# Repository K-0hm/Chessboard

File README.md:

# TactBoard
Code for a chessboard with light and capacitance Touch Sensors.

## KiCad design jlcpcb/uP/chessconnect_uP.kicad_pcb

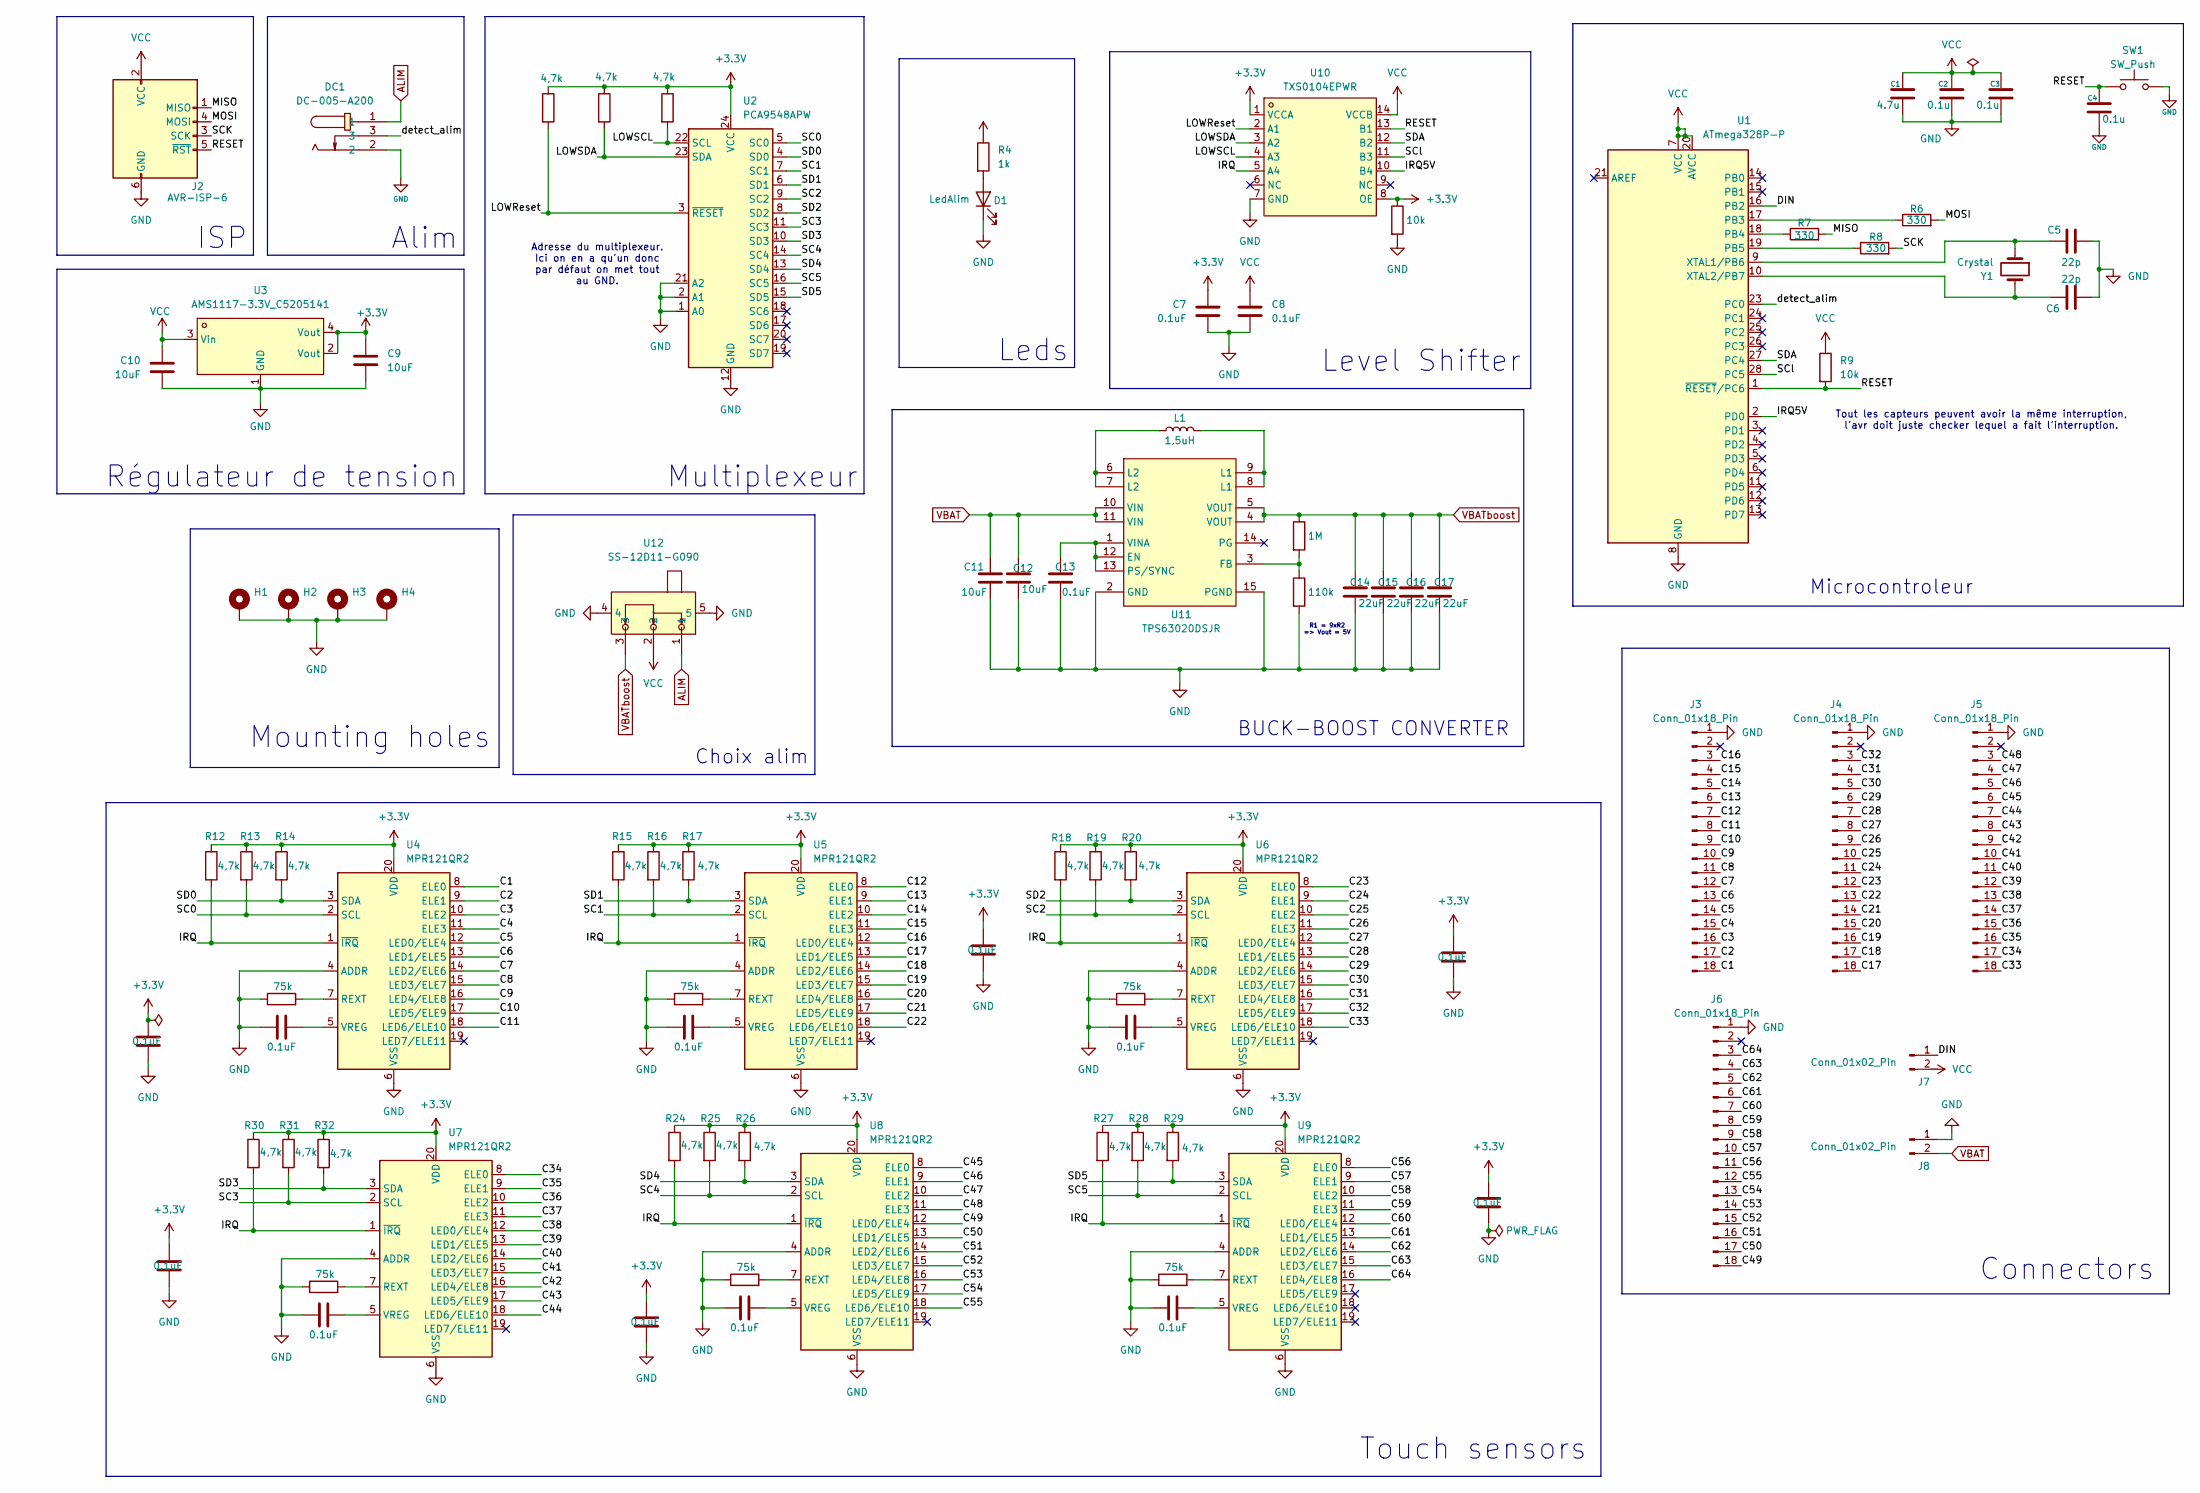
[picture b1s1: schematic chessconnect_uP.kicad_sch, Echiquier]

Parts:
C1: 4.7u; C_0603_1608Metric_Pad1.08x0.95mm_HandSolder
C2, C3, C4: 0.1u; C_0603_1608Metric_Pad1.08x0.95mm_HandSolder
C5, C6: 22p; C_0603_1608Metric_Pad1.08x0.95mm_HandSolder
C7, C8, C13, C18, C19, C20, C21, C22, C23, C24, C25, C26, C27, C28, C29: 0.1uF; C_0603_1608Metric_Pad1.08x0.95mm_HandSolder
C9, C10, C11, C12: 10uF; C_0603_1608Metric_Pad1.08x0.95mm_HandSolder
C14, C15, C16, C17: 22uF; C_0603_1608Metric_Pad1.08x0.95mm_HandSolder
D1: LedAlim; LED_0201_0603Metric_Pad0.64x0.40mm_HandSolder
DC1: DC-005-A200; DC-IN-TH_DC-005-A200; MPN DC-005-A200; LCSC Part C720557
H1, H2, H3, H4: MountingHole_Pad; MountingHole_3.2mm_M3_DIN965_Pad
J2: AVR-ISP-6; PinSocket_2x03_P2.54mm_Vertical
J3, J4, J5, J6: Conn_01x18_Pin; FPC-SMD_18P-P1.00_XUNPU_FPC-1.0FX-18PWCR-H20
J7, J8: Conn_01x02_Pin; PinHeader_1x02_P2.54mm_Horizontal
L1: 1,5uH; IND-SMD_L4.0-W4.0-A
R1, R2, R3, R12, R13, R14, R15, R16, R17, R18, R19, R20, R24, R25, R26, R27, R28, R29, R30, R31, R32: 4,7k; R_0603_1608Metric_Pad0.98x0.95mm_HandSolder
R4: 1k; R_0603_1608Metric_Pad0.98x0.95mm_HandSolder
R5, R9: 10k; R_0603_1608Metric_Pad0.98x0.95mm_HandSolder
R6, R7, R8: 330; R_0603_1608Metric_Pad0.98x0.95mm_HandSolder
R10: 1M; R_0603_1608Metric_Pad0.98x0.95mm_HandSolder
R11: 110k; R_0603_1608Metric_Pad0.98x0.95mm_HandSolder
R21, R22, R23, R33, R34, R35: 75k; R_0603_1608Metric_Pad0.98x0.95mm_HandSolder
SW1: SW_Push; SW_PUSH_6mm_H8mm
U1: ATmega328P-P; DIP-28_W7.62mm
U2: PCA9548APW; TSSOP-24_L7.8-W4.4-P0.65-LS6.4-BL
U3: AMS1117-3.3V_C5205141; SOT-223-3_L6.5-W3.4-P2.30-LS7.0-BR; MPN AMS1117-3.3V; LCSC Part C5205141
U4, U5, U6, U7, U8, U9: MPR121QR2; UQFN-20_3x3mm_P0.4mm
U10: TXS0104EPWR; TSSOP-14_L5.0-W4.4-P0.65-LS6.4-BL; MPN TXS0104EPWR; LCSC Part C44955
U11: TPS63020DSJR; VSON-14_L4.0-W3.0-P0.50-BL-EP_TI_DSJ; MPN TPS63020DSJR; LCSC Part C15483
U12: SS-12D11-G090; SW-TH_5P-P4.70_SS-12D11-G090; MPN SS-12D11-G090; LCSC Part C17179532
Y1: Crystal; Crystal_HC49-4H_Vertical

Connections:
+3.3V: C7.1, C9.1, C18.2, C19.2, C23.2, C24.2, C25.2, C29.2, R1.1, R2.1, R3.1, R5.1, R12.1, R13.1, R14.1, R15.1, R16.1, R17.1, R18.1, R19.1, R20.1, R24.1, R25.1, R26.1, R27.1, R28.1, R29.1, R30.1, R31.1, R32.1, U2.24 (VCC), U3.2 (Vout), U3.4 (Vout), U4.20 (VDD), U5.20 (VDD), U6.20 (VDD), U7.20 (VDD), U8.20 (VDD), U9.20 (VDD), U10.1 (VCCA), U10.8 (OE)
/C1: J3.18, U4.8 (ELE0)
/C2: J3.17, U4.9 (ELE1)
/C3: J3.16, U4.10 (ELE2)
/C4: J3.15, U4.11 (ELE3)
/C5: J3.14, U4.12 (LED0/ELE4)
/C6: J3.13, U4.13 (LED1/ELE5)
/C7: J3.12, U4.14 (LED2/ELE6)
/C8: J3.11, U4.15 (LED3/ELE7)
/C9: J3.10, U4.16 (LED4/ELE8)
/C10: J3.9, U4.17 (LED5/ELE9)
/C11: J3.8, U4.18 (LED6/ELE10)
/C12: J3.7, U5.8 (ELE0)
/C13: J3.6, U5.9 (ELE1)
/C14: J3.5, U5.10 (ELE2)
/C15: J3.4, U5.11 (ELE3)
/C16: J3.3, U5.12 (LED0/ELE4)
/C17: J4.18, U5.13 (LED1/ELE5)
/C18: J4.17, U5.14 (LED2/ELE6)
/C19: J4.16, U5.15 (LED3/ELE7)
/C20: J4.15, U5.16 (LED4/ELE8)
/C21: J4.14, U5.17 (LED5/ELE9)
/C22: J4.13, U5.18 (LED6/ELE10)
/C23: J4.12, U6.8 (ELE0)
/C24: J4.11, U6.9 (ELE1)
/C25: J4.10, U6.10 (ELE2)
/C26: J4.9, U6.11 (ELE3)
/C27: J4.8, U6.12 (LED0/ELE4)
/C28: J4.7, U6.13 (LED1/ELE5)
/C29: J4.6, U6.14 (LED2/ELE6)
/C30: J4.5, U6.15 (LED3/ELE7)
/C31: J4.4, U6.16 (LED4/ELE8)
/C32: J4.3, U6.17 (LED5/ELE9)
/C33: J5.18, U6.18 (LED6/ELE10)
/C34: J5.17, U7.8 (ELE0)
/C35: J5.16, U7.9 (ELE1)
/C36: J5.15, U7.10 (ELE2)
/C37: J5.14, U7.11 (ELE3)
/C38: J5.13, U7.12 (LED0/ELE4)
/C39: J5.12, U7.13 (LED1/ELE5)
/C40: J5.11, U7.14 (LED2/ELE6)
/C41: J5.10, U7.15 (LED3/ELE7)
/C42: J5.9, U7.16 (LED4/ELE8)
/C43: J5.8, U7.17 (LED5/ELE9)
/C44: J5.7, U7.18 (LED6/ELE10)
/C45: J5.6, U8.8 (ELE0)
/C46: J5.5, U8.9 (ELE1)
/C47: J5.4, U8.10 (ELE2)
/C48: J5.3, U8.11 (ELE3)
/C49: J6.18, U8.12 (LED0/ELE4)
/C50: J6.17, U8.13 (LED1/ELE5)
/C51: J6.16, U8.14 (LED2/ELE6)
/C52: J6.15, U8.15 (LED3/ELE7)
/C53: J6.14, U8.16 (LED4/ELE8)
/C54: J6.13, U8.17 (LED5/ELE9)
/C55: J6.12, U8.18 (LED6/ELE10)
/C56: J6.11, U9.8 (ELE0)
/C57: J6.10, U9.9 (ELE1)
/C58: J6.9, U9.10 (ELE2)
/C59: J6.8, U9.11 (ELE3)
/C60: J6.7, U9.12 (LED0/ELE4)
/C61: J6.6, U9.13 (LED1/ELE5)
/C62: J6.5, U9.14 (LED2/ELE6)
/C63: J6.4, U9.15 (LED3/ELE7)
/C64: J6.3, U9.16 (LED4/ELE8)
/DIN: J7.1, U1.16 (PB2)
/IRQ: R12.2, R15.2, R18.2, R24.2, R27.2, R30.2, U4.1 (~IRQ), U5.1 (~IRQ), U6.1 (~IRQ), U7.1 (~IRQ), U8.1 (~IRQ), U9.1 (~IRQ), U10.5 (A4)
/IRQ5V: U1.2 (PD0), U10.10 (B4)
/LOWReset: R1.2, U2.3 (~RESET), U10.2 (A1)
/LOWSCL: R3.2, U2.22 (SCL), U10.4 (A3)
/LOWSDA: R2.2, U2.23 (SDA), U10.3 (A2)
/MISO: J2.1 (MISO), R7.2
/MOSI: J2.4 (MOSI), R6.2
/RESET: C4.1, J2.5 (~RST), R9.2, SW1.1, U1.1 (~RESET/PC6), U10.13 (B1)
/SC0: R13.2, U2.5 (SC0), U4.2 (SCL)
/SC1: R16.2, U2.7 (SC1), U5.2 (SCL)
/SC2: R19.2, U2.9 (SC2), U6.2 (SCL)
/SC3: R31.2, U2.11 (SC3), U7.2 (SCL)
/SC4: R25.2, U2.14 (SC4), U8.2 (SCL)
/SC5: R28.2, U2.16 (SC5), U9.2 (SCL)
/SCK: J2.3 (SCK), R8.2
/SCl: U1.28 (PC5), U10.11 (B3)
/SD0: R14.2, U2.4 (SD0), U4.3 (SDA)
/SD1: R17.2, U2.6 (SD1), U5.3 (SDA)
/SD2: R20.2, U2.8 (SD2), U6.3 (SDA)
/SD3: R32.2, U2.10 (SD3), U7.3 (SDA)
/SD4: R26.2, U2.13 (SD4), U8.3 (SDA)
/SD5: R29.2, U2.15 (SD5), U9.3 (SDA)
/SDA: U1.27 (PC4), U10.12 (B2)
/detect_alim: DC1.3, U1.23 (PC0)
ALIM: DC1.1, U12.1
GND: C1.1, C2.1, C3.1, C4.2, C5.1, C6.1, C7.2, C8.2, C9.2, C10.2, C11.2, C12.2, C13.2, C14.2, C15.2, C16.2, C17.2, C18.1, C19.1, C20.2, C21.2, C22.2, C23.1, C24.1, C25.1, C26.2, C27.2, C28.2, C29.1, D1.1 (K), DC1.2, H1.1, H2.1, H3.1, H4.1, J2.6 (GND), J3.1, J4.1, J5.1, J6.1, J8.1, R5.2, R11.2, R21.1, R22.1, R23.1, R33.1, R34.1, R35.1, SW1.2, U1.8 (GND), U1.22 (GND), U2.1 (A0), U2.2 (A1), U2.12 (GND), U2.21 (A2), U3.1 (GND), U4.4 (ADDR), U4.6 (VSS), U5.4 (ADDR), U5.6 (VSS), U6.4 (ADDR), U6.6 (VSS), U7.4 (ADDR), U7.6 (VSS), U8.4 (ADDR), U8.6 (VSS), U9.4 (ADDR), U9.6 (VSS), U10.7 (GND), U11.2 (GND), U11.15 (PGND), U12.4, U12.5
unnamed: D1.2 (A), R4.2
unnamed: L1.1, U11.6 (L2), U11.7 (L2)
unnamed: L1.2, U11.8 (L1), U11.9 (L1)
unnamed: R6.1, U1.17 (PB3)
unnamed: R7.1, U1.18 (PB4)
unnamed: R8.1, U1.19 (PB5)
unnamed: C5.2, U1.9 (XTAL1/PB6), Y1.1
unnamed: C6.2, U1.10 (XTAL2/PB7), Y1.2
unnamed: R21.2, U4.7 (REXT)
unnamed: C20.1, U4.5 (VREG)
unnamed: R22.2, U5.7 (REXT)
unnamed: C21.1, U5.5 (VREG)
unnamed: R23.2, U6.7 (REXT)
unnamed: C22.1, U6.5 (VREG)
unnamed: R35.2, U7.7 (REXT)
unnamed: C28.1, U7.5 (VREG)
unnamed: R33.2, U8.7 (REXT)
unnamed: C26.1, U8.5 (VREG)
unnamed: R34.2, U9.7 (REXT)
unnamed: C27.1, U9.5 (VREG)
unnamed: C13.1, U11.1 (VINA), U11.12 (EN), U11.13 (PS/SYNC)
unnamed: R10.2, R11.1, U11.3 (FB)
VBAT: C11.1, C12.1, J8.2, U11.10 (VIN), U11.11 (VIN)
VBATboost: C14.1, C15.1, C16.1, C17.1, R10.1, U11.4 (VOUT), U11.5 (VOUT), U12.3
VCC: C1.2, C2.2, C3.2, C8.1, C10.1, J2.2 (VCC), J7.2, R4.1, R9.1, U1.7 (VCC), U1.20 (AVCC), U3.3 (Vin), U10.14 (VCCB), U12.2

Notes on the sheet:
Adresse du multiplexeur. Ici on en a qu'un donc par défaut on met tout au GND.
Microcontroleur
Level Shifter
Tout les capteurs peuvent avoir la même interruption, l'avr doit juste checker lequel a fait l'interruption.
R1 = 9xR2 => Vout = 5V
Mounting holes
Choix alim
Connectors
Touch sensors
BUCK-BOOST CONVERTER
Alim
Leds
Régulateur de tension
ISP
Multiplexeur

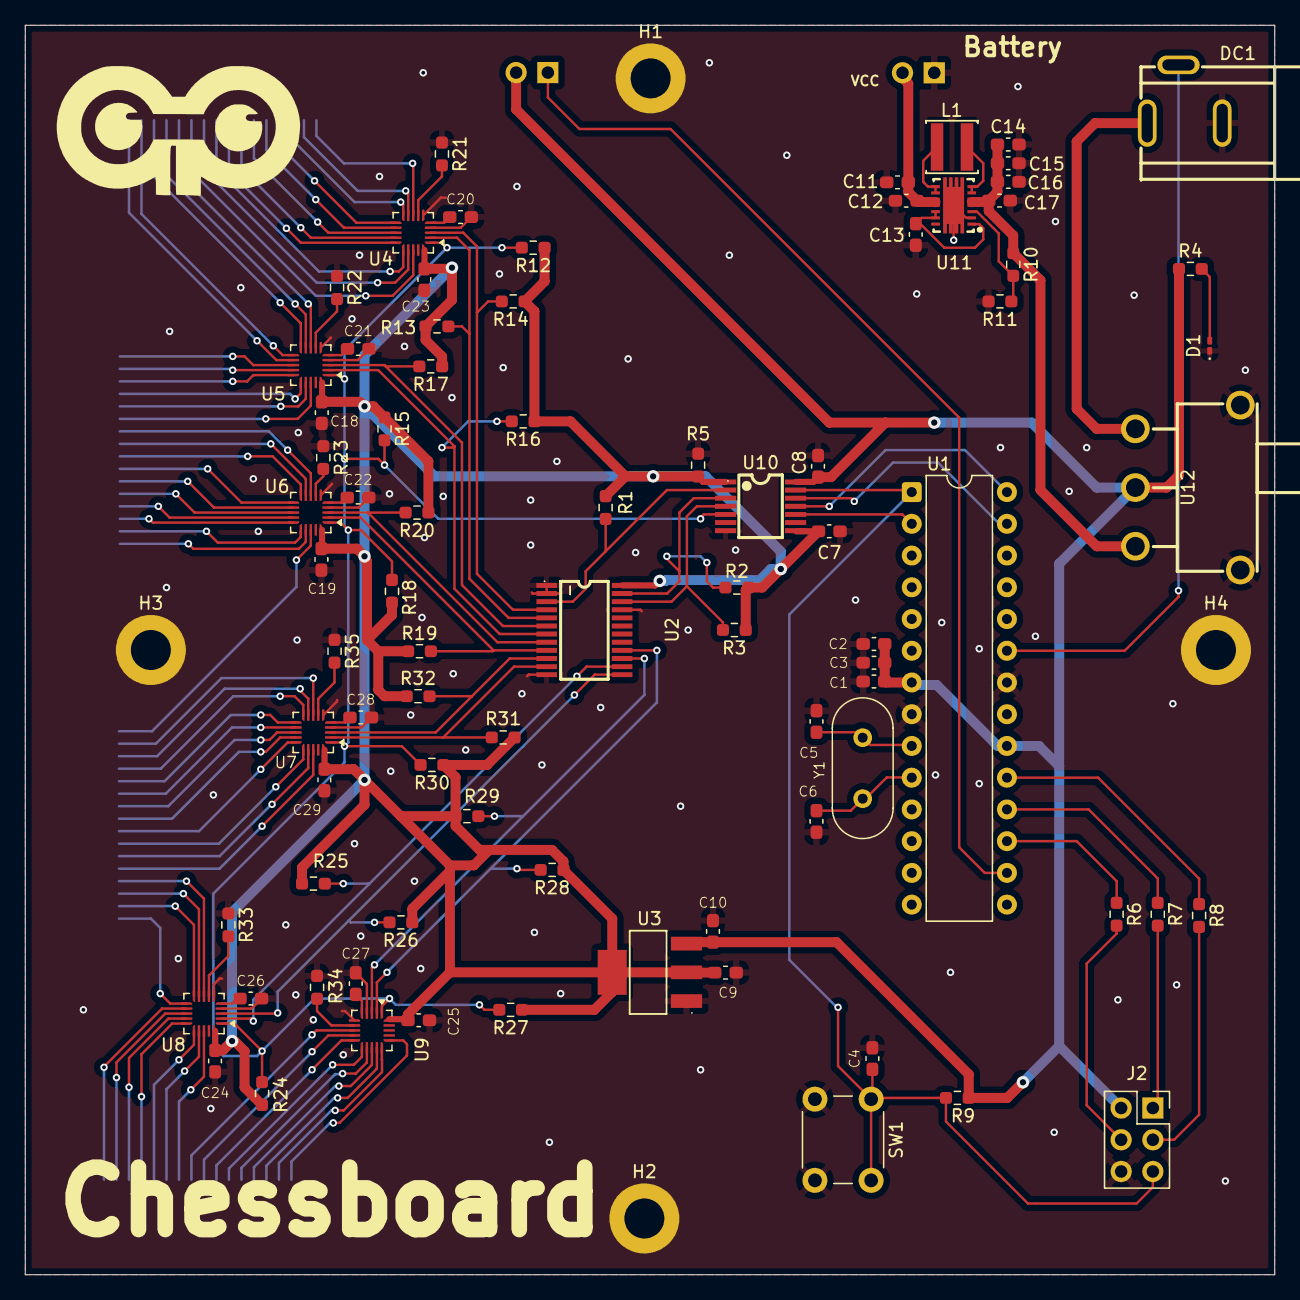
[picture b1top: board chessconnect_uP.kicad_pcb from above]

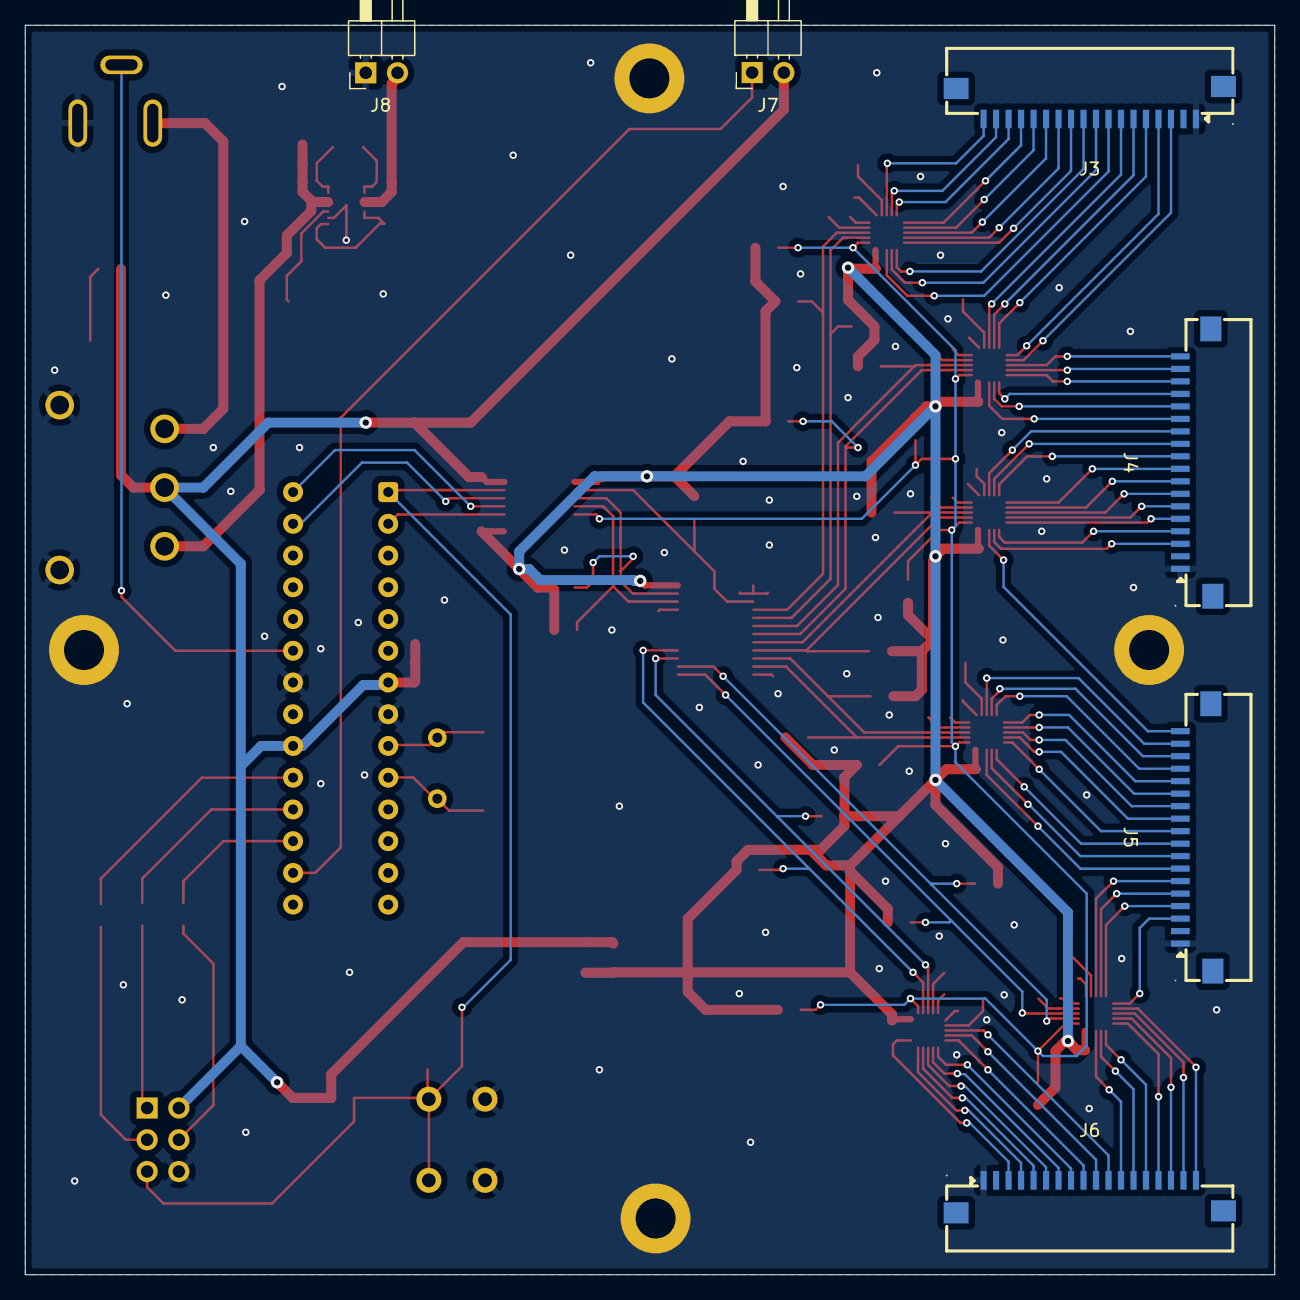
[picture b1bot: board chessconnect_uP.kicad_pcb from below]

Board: 2 copper layers, 100.0 x 100.0 mm, 92 parts (6 on the bottom side), 117 nets.

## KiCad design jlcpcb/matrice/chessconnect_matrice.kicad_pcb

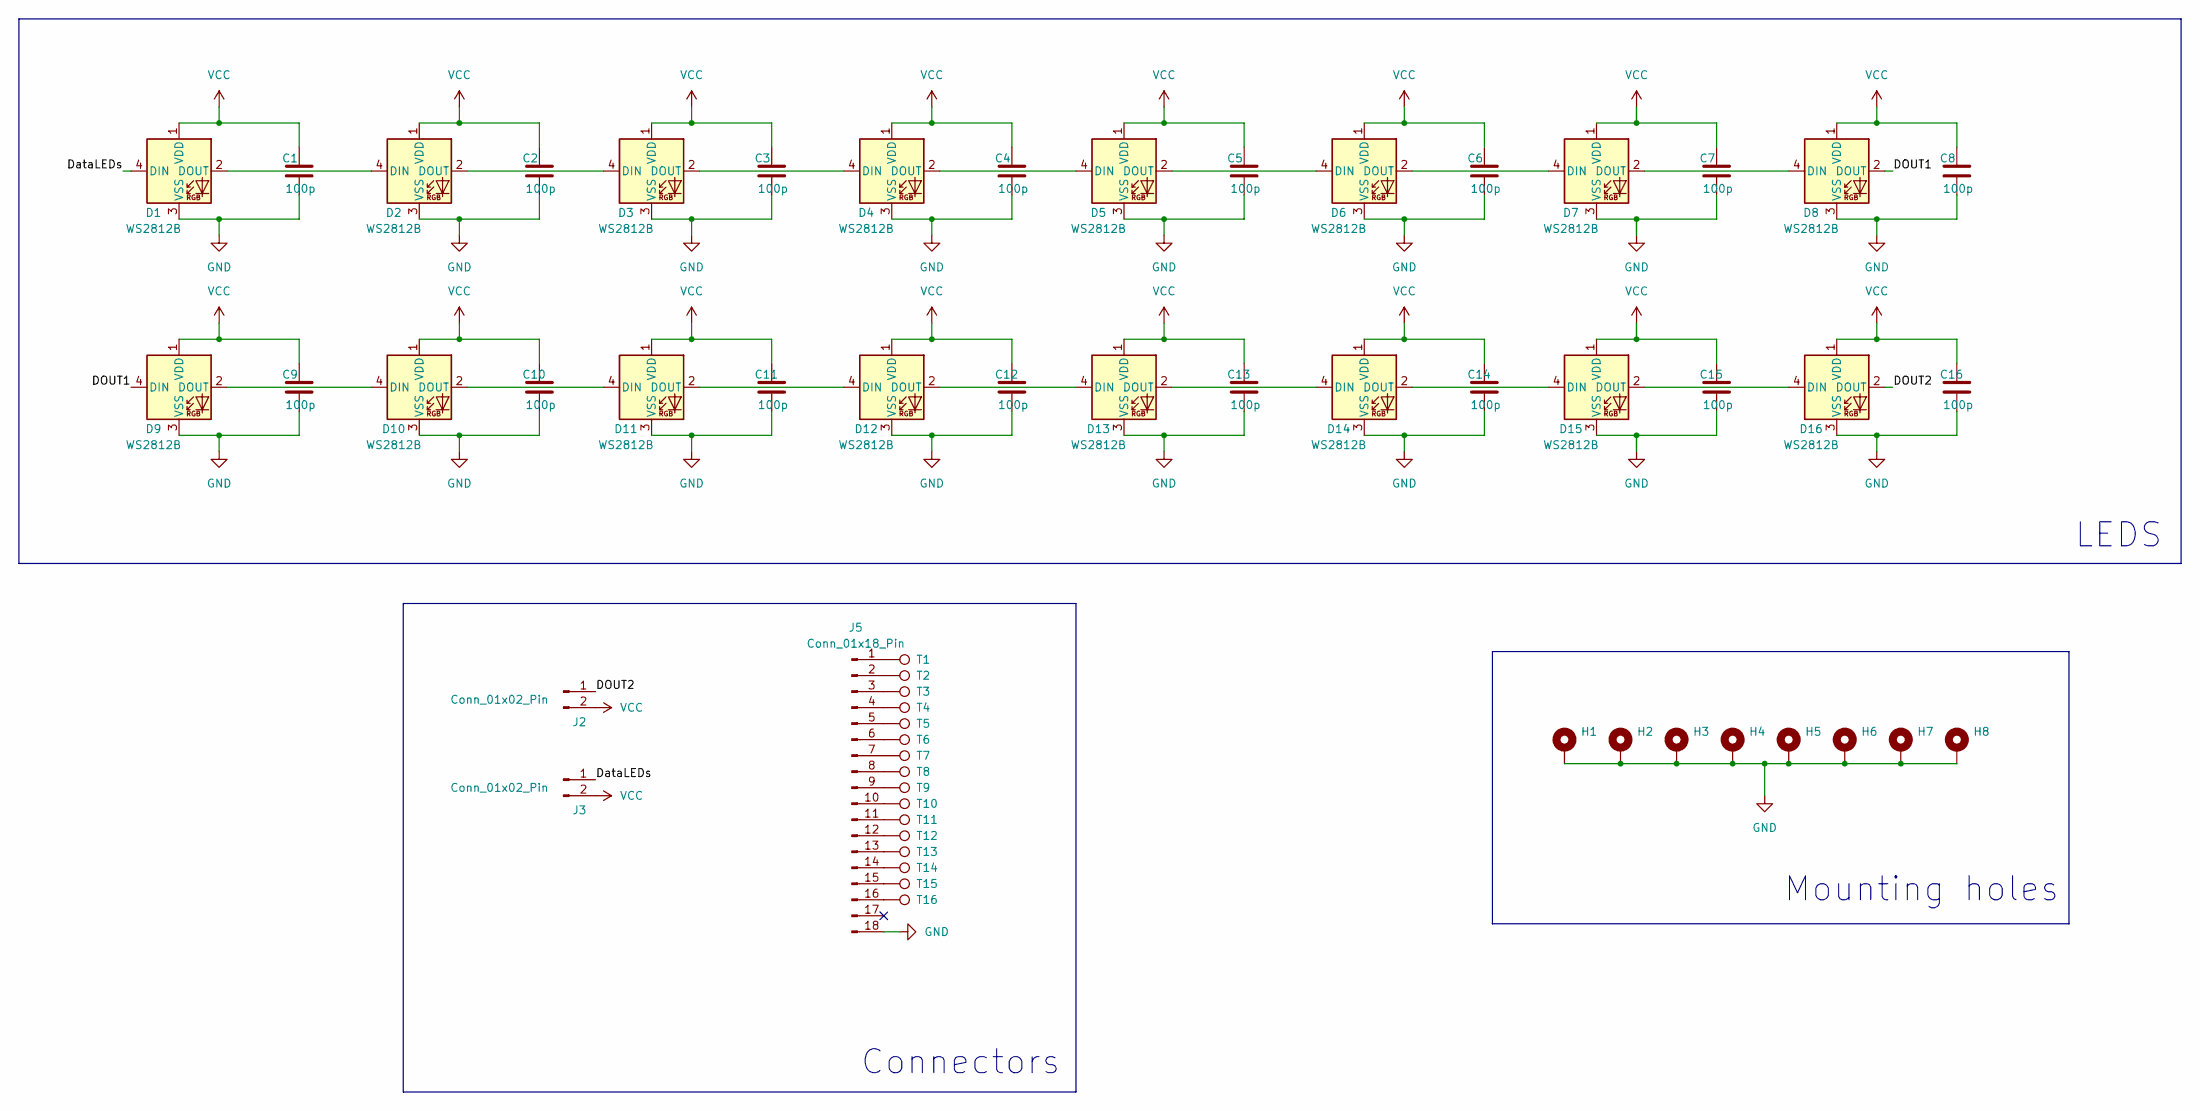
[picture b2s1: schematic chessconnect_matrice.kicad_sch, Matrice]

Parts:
C1, C2, C3, C4, C5, C6, C7, C8, C9, C10, C11, C12, C13, C14, C15, C16: 100p; C_0402_1005Metric_Pad0.74x0.62mm_HandSolder
D1, D2, D3, D4, D5, D6, D7, D8, D9, D10, D11, D12, D13, D14, D15, D16: WS2812B; LED_WS2812B_PLCC4_5.0x5.0mm_P3.2mm
H1, H2, H3, H4, H5, H6, H7, H8: MountingHole_Pad; MountingHole_3.2mm_M3_Pad
J2, J3: Conn_01x02_Pin; PinHeader_1x02_P2.54mm_Vertical
J5: Conn_01x18_Pin; FPC-SMD_18P-P1.00_XUNPU_FPC-1.0FX-18PWCR-H20
T1, T2, T3, T4, T5, T6, T7, T8, T9, T10, T11, T12, T13, T14, T15, T16: TestPoint; TestPoint_Pad_4.0x4.0mm

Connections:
/DOUT1: D8.2 (DOUT), D9.4 (DIN)
/DOUT2: D16.2 (DOUT), J2.1
/DataLEDs: D1.4 (DIN), J3.1
GND: C1.2, C2.2, C3.2, C4.2, C5.2, C6.2, C7.2, C8.2, C9.2, C10.2, C11.2, C12.2, C13.2, C14.2, C15.2, C16.2, D1.3 (VSS), D2.3 (VSS), D3.3 (VSS), D4.3 (VSS), D5.3 (VSS), D6.3 (VSS), D7.3 (VSS), D8.3 (VSS), D9.3 (VSS), D10.3 (VSS), D11.3 (VSS), D12.3 (VSS), D13.3 (VSS), D14.3 (VSS), D15.3 (VSS), D16.3 (VSS), H1.1, H2.1, H3.1, H4.1, H5.1, H6.1, H7.1, H8.1, J5.18
unnamed: D1.2 (DOUT), D2.4 (DIN)
unnamed: D2.2 (DOUT), D3.4 (DIN)
unnamed: D3.2 (DOUT), D4.4 (DIN)
unnamed: D4.2 (DOUT), D5.4 (DIN)
unnamed: D5.2 (DOUT), D6.4 (DIN)
unnamed: D6.2 (DOUT), D7.4 (DIN)
unnamed: D7.2 (DOUT), D8.4 (DIN)
unnamed: D9.2 (DOUT), D10.4 (DIN)
unnamed: D10.2 (DOUT), D11.4 (DIN)
unnamed: D11.2 (DOUT), D12.4 (DIN)
unnamed: D12.2 (DOUT), D13.4 (DIN)
unnamed: D13.2 (DOUT), D14.4 (DIN)
unnamed: D14.2 (DOUT), D15.4 (DIN)
unnamed: D15.2 (DOUT), D16.4 (DIN)
unnamed: J5.1, T1.1
unnamed: J5.2, T2.1
unnamed: J5.3, T3.1
unnamed: J5.4, T4.1
unnamed: J5.5, T5.1
unnamed: J5.6, T6.1
unnamed: J5.7, T7.1
unnamed: J5.8, T8.1
unnamed: J5.9, T9.1
unnamed: J5.10, T10.1
unnamed: J5.11, T11.1
unnamed: J5.12, T12.1
unnamed: J5.13, T13.1
unnamed: J5.14, T14.1
unnamed: J5.15, T15.1
unnamed: J5.16, T16.1
VCC: C1.1, C2.1, C3.1, C4.1, C5.1, C6.1, C7.1, C8.1, C9.1, C10.1, C11.1, C12.1, C13.1, C14.1, C15.1, C16.1, D1.1 (VDD), D2.1 (VDD), D3.1 (VDD), D4.1 (VDD), D5.1 (VDD), D6.1 (VDD), D7.1 (VDD), D8.1 (VDD), D9.1 (VDD), D10.1 (VDD), D11.1 (VDD), D12.1 (VDD), D13.1 (VDD), D14.1 (VDD), D15.1 (VDD), D16.1 (VDD), J2.2, J3.2

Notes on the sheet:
Connectors
LEDS
Mounting holes

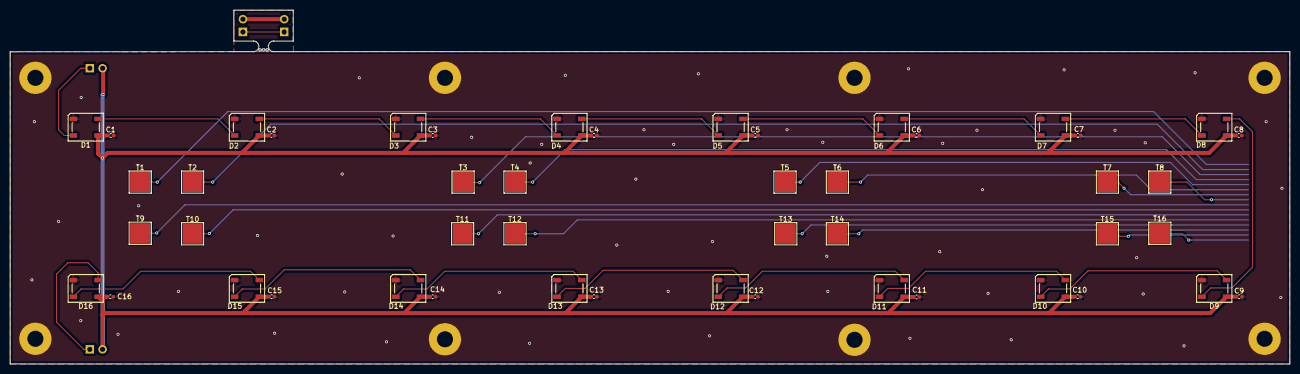
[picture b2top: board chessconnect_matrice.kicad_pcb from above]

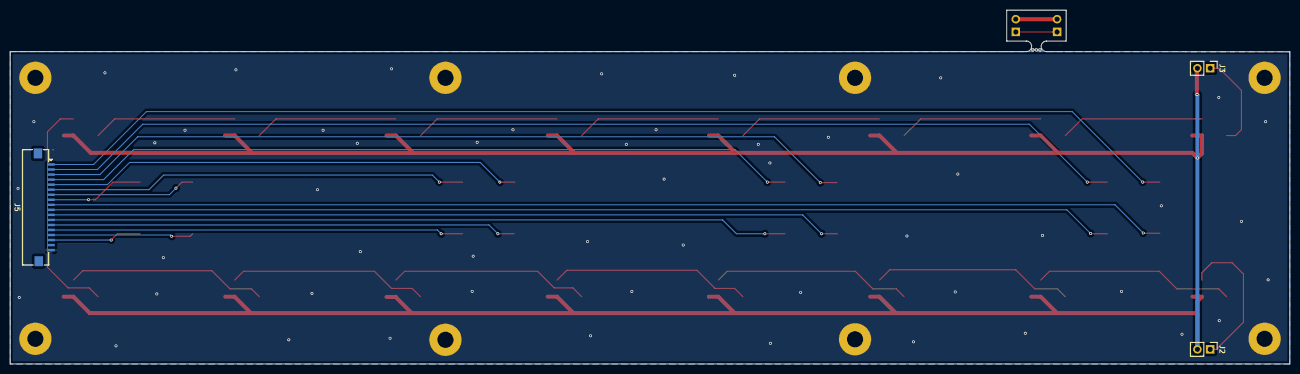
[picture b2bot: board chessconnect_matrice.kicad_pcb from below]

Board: 2 copper layers, 254.0 x 70.2 mm, 59 parts (3 on the bottom side), 35 nets.

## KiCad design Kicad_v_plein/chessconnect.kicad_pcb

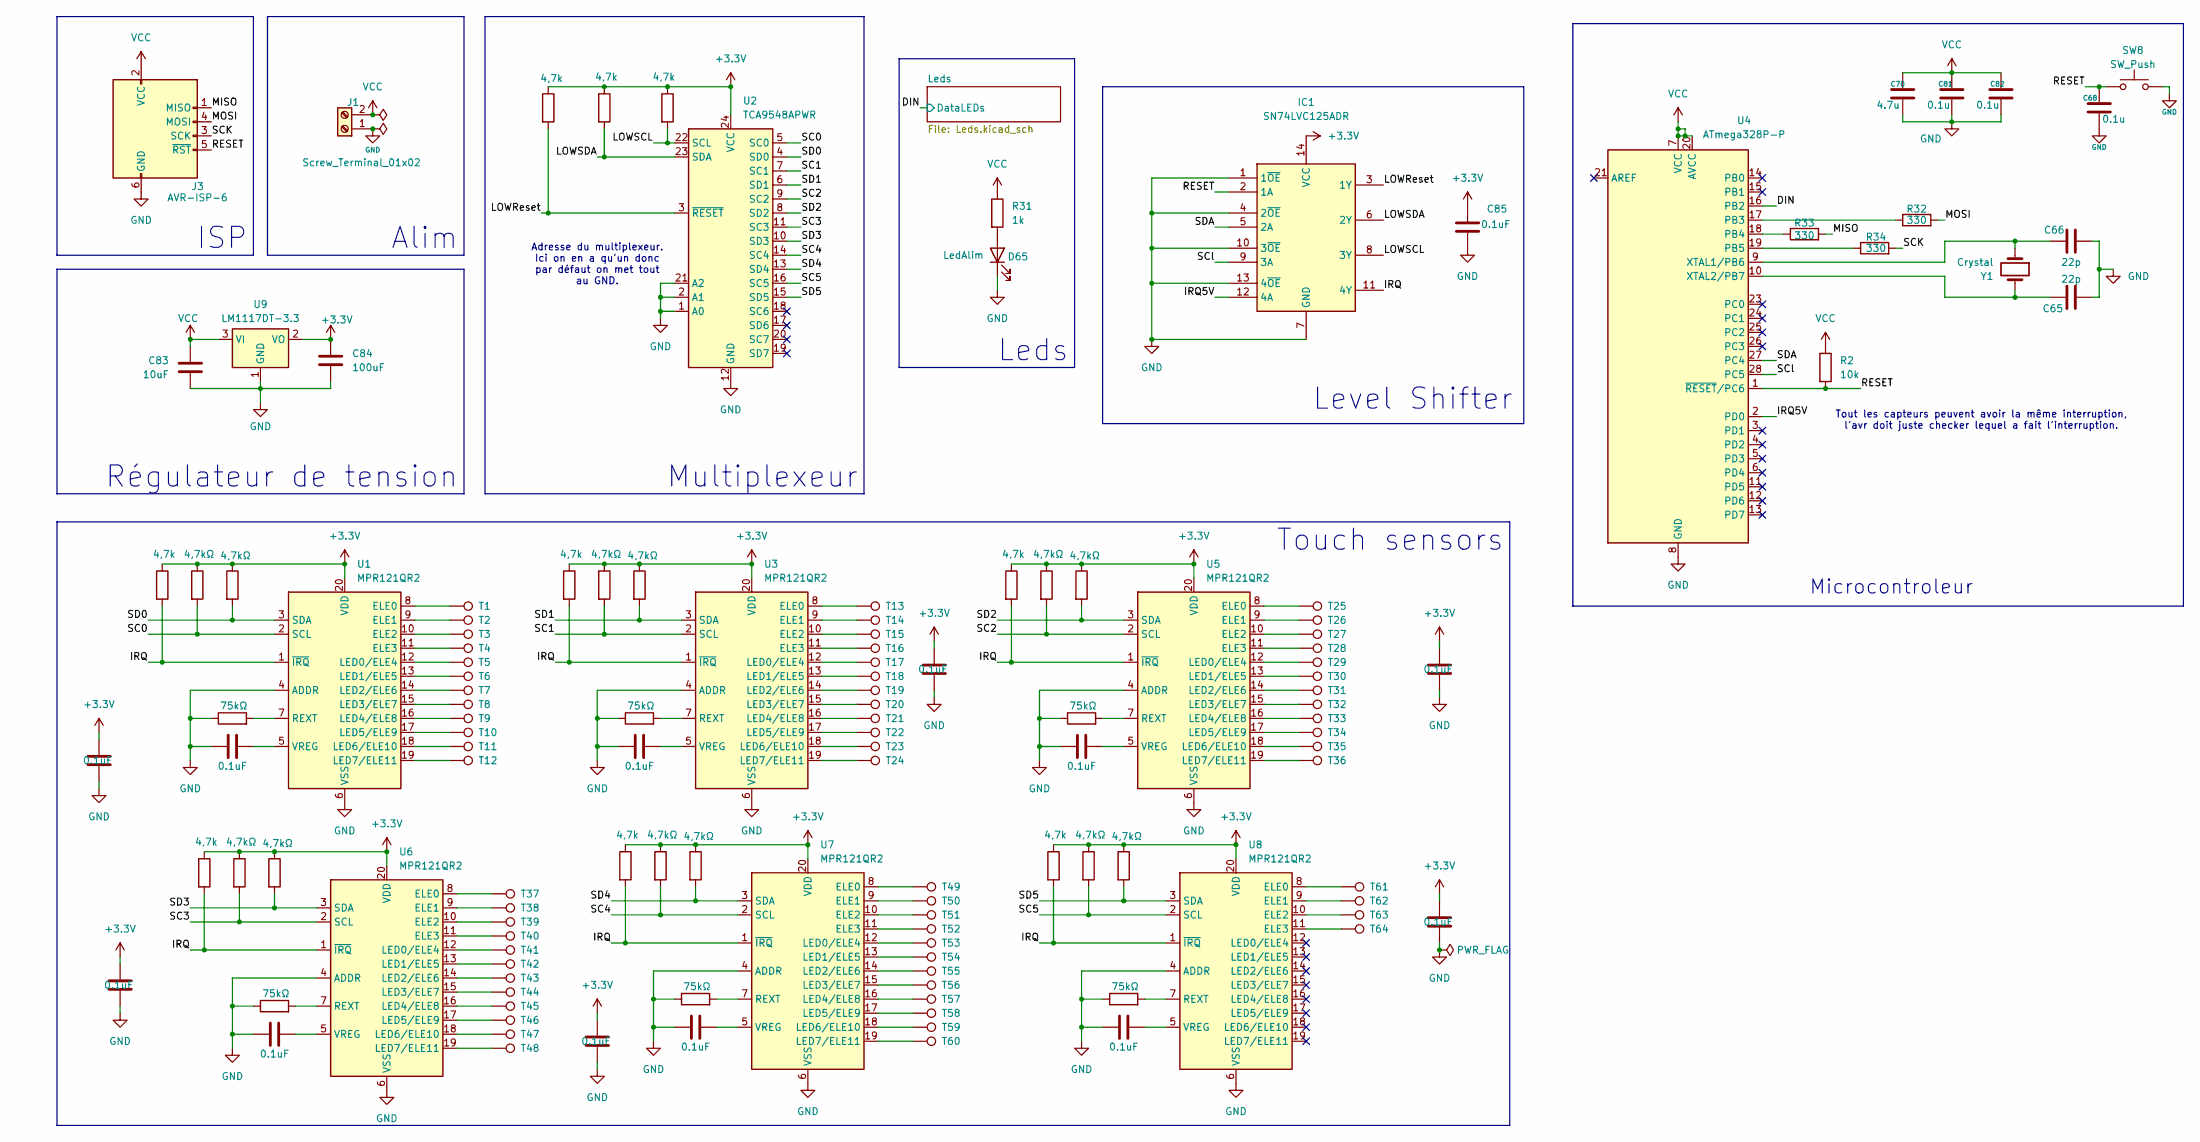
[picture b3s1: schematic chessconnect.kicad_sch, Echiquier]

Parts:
C65, C66: 22p; C_0603_1608Metric_Pad1.08x0.95mm_HandSolder
C67, C69, C71, C72, C73, C74, C75, C76, C77, C78, C79, C80, C85: 0.1uF; C_0603_1608Metric_Pad1.08x0.95mm_HandSolder
C68, C81, C82: 0.1u; C_0603_1608Metric_Pad1.08x0.95mm_HandSolder
C70: 4.7u; C_0603_1608Metric_Pad1.08x0.95mm_HandSolder
C83: 10uF; C_0603_1608Metric_Pad1.08x0.95mm_HandSolder
C84: 100uF; C_0603_1608Metric_Pad1.08x0.95mm_HandSolder
D65: LedAlim; LED_0201_0603Metric_Pad0.64x0.40mm_HandSolder
IC1: SN74LVC125ADR; SOIC74LVC125; Manufacturer_Part_Number SN74LVC125ADR
J1: Screw_Terminal_01x02; TerminalBlock_Phoenix_MKDS-3-2-5.08_1x02_P5.08mm_Horizontal
J3: AVR-ISP-6; PinSocket_2x03_P2.54mm_Vertical
R1, R4, R12, R13, R16, R17, R20, R21, R24, R25, R28, R29: 4,7kΩ; R_1206_3216Metric_Pad1.30x1.75mm_HandSolder
R2: 10k; R_1206_3216Metric_Pad1.30x1.75mm_HandSolder
R5, R14, R18, R22, R26, R30: 75kΩ; R_1206_3216Metric_Pad1.30x1.75mm_HandSolder
R6, R7, R8, R9, R11, R15, R19, R23, R27: 4,7k; R_1206_3216Metric_Pad1.30x1.75mm_HandSolder
R31: 1k; R_1206_3216Metric_Pad1.30x1.75mm_HandSolder
R32, R33, R34: 330; R_1206_3216Metric_Pad1.30x1.75mm_HandSolder
SW8: SW_Push; SW_PUSH_6mm_H8mm
T1, T2, T3, T4, T5, T6, T7, T8, T9, T10, T11, T12, T13, T14, T15, T16, T17, T18, T19, T20, T21, T22, T23, T24, T25, T26, T27, T28, T29, T30, T31, T32, T33, T34, T35, T36, T37, T38, T39, T40, T41, T42, T43, T44, T45, T46, T47, T48, T49, T50, T51, T52, T53, T54, T55, T56, T57, T58, T59, T60, T61, T62, T63, T64: TestPoint; TestPoint_Pad_4.0x4.0mm
U1, U3, U5, U6, U7, U8: MPR121QR2; UQFN-20_3x3mm_P0.4mm
U2: TCA9548APWR; TSSOP-24_4.4x7.8mm_P0.65mm
U4: ATmega328P-P; DIP-28_W7.62mm
U9: LM1117DT-3.3; TO-252-3_TabPin2
Y1: Crystal; Crystal_HC49-4H_Vertical

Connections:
+3.3V: C75.2, C76.2, C77.2, C78.2, C79.2, C80.2, C84.1, C85.2, IC1.14 (VCC), R1.1, R4.1, R6.1, R7.1, R8.1, R9.1, R11.1, R12.1, R13.1, R15.1, R16.1, R17.1, R19.1, R20.1, R21.1, R23.1, R24.1, R25.1, R27.1, R28.1, R29.1, U1.20 (VDD), U2.24 (VCC), U3.20 (VDD), U5.20 (VDD), U6.20 (VDD), U7.20 (VDD), U8.20 (VDD), U9.2 (VO)
/DIN: U4.16 (PB2); also elsewhere on the board
/IRQ: IC1.11 (4Y), R6.2, R11.2, R15.2, R19.2, R23.2, R27.2, U1.1 (~IRQ), U3.1 (~IRQ), U5.1 (~IRQ), U6.1 (~IRQ), U7.1 (~IRQ), U8.1 (~IRQ)
/IRQ5V: IC1.12 (4A), U4.2 (PD0)
/LOWReset: IC1.3 (1Y), R9.2, U2.3 (~RESET)
/LOWSCL: IC1.8 (3Y), R7.2, U2.22 (SCL)
/LOWSDA: IC1.6 (2Y), R8.2, U2.23 (SDA)
/MISO: J3.1 (MISO), R33.2
/MOSI: J3.4 (MOSI), R32.2
/RESET: C68.1, IC1.2 (1A), J3.5 (~RST), R2.2, SW8.1, U4.1 (~RESET/PC6)
/SC0: R4.2, U1.2 (SCL), U2.5 (SC0)
/SC1: R12.2, U2.7 (SC1), U3.2 (SCL)
/SC2: R16.2, U2.9 (SC2), U5.2 (SCL)
/SC3: R20.2, U2.11 (SC3), U6.2 (SCL)
/SC4: R24.2, U2.14 (SC4), U7.2 (SCL)
/SC5: R28.2, U2.16 (SC5), U8.2 (SCL)
/SCK: J3.3 (SCK), R34.2
/SCl: IC1.9 (3A), U4.28 (PC5)
/SD0: R1.2, U1.3 (SDA), U2.4 (SD0)
/SD1: R13.2, U2.6 (SD1), U3.3 (SDA)
/SD2: R17.2, U2.8 (SD2), U5.3 (SDA)
/SD3: R21.2, U2.10 (SD3), U6.3 (SDA)
/SD4: R25.2, U2.13 (SD4), U7.3 (SDA)
/SD5: R29.2, U2.15 (SD5), U8.3 (SDA)
/SDA: IC1.5 (2A), U4.27 (PC4)
GND: C65.1, C66.1, C67.2, C68.2, C69.2, C70.1, C71.2, C72.2, C73.2, C74.2, C75.1, C76.1, C77.1, C78.1, C79.1, C80.1, C81.1, C82.1, C83.2, C84.2, C85.1, D65.1 (K), IC1.1 (1~OE), IC1.4 (2~OE), IC1.7 (GND), IC1.10 (3~OE), IC1.13 (4~OE), J1.1, J3.6 (GND), R5.1, R14.1, R18.1, R22.1, R26.1, R30.1, SW8.2, U1.4 (ADDR), U1.6 (VSS), U2.1 (A0), U2.2 (A1), U2.12 (GND), U2.21 (A2), U3.4 (ADDR), U3.6 (VSS), U4.8 (GND), U4.22 (GND), U5.4 (ADDR), U5.6 (VSS), U6.4 (ADDR), U6.6 (VSS), U7.4 (ADDR), U7.6 (VSS), U8.4 (ADDR), U8.6 (VSS), U9.1 (GND); also elsewhere on the board
unnamed: D65.2 (A), R31.2
unnamed: T1.1, U1.8 (ELE0)
unnamed: T2.1, U1.9 (ELE1)
unnamed: T3.1, U1.10 (ELE2)
unnamed: T4.1, U1.11 (ELE3)
unnamed: T5.1, U1.12 (LED0/ELE4)
unnamed: T6.1, U1.13 (LED1/ELE5)
unnamed: T7.1, U1.14 (LED2/ELE6)
unnamed: T8.1, U1.15 (LED3/ELE7)
unnamed: T9.1, U1.16 (LED4/ELE8)
unnamed: T10.1, U1.17 (LED5/ELE9)
unnamed: T11.1, U1.18 (LED6/ELE10)
unnamed: T12.1, U1.19 (LED7/ELE11)
unnamed: R5.2, U1.7 (REXT)
unnamed: C71.1, U1.5 (VREG)
unnamed: T13.1, U3.8 (ELE0)
unnamed: T14.1, U3.9 (ELE1)
unnamed: T15.1, U3.10 (ELE2)
unnamed: T16.1, U3.11 (ELE3)
unnamed: T17.1, U3.12 (LED0/ELE4)
unnamed: T18.1, U3.13 (LED1/ELE5)
unnamed: T19.1, U3.14 (LED2/ELE6)
unnamed: T20.1, U3.15 (LED3/ELE7)
unnamed: T21.1, U3.16 (LED4/ELE8)
unnamed: T22.1, U3.17 (LED5/ELE9)
unnamed: T23.1, U3.18 (LED6/ELE10)
unnamed: T24.1, U3.19 (LED7/ELE11)
unnamed: R14.2, U3.7 (REXT)
unnamed: C67.1, U3.5 (VREG)
unnamed: R32.1, U4.17 (PB3)
unnamed: R33.1, U4.18 (PB4)
unnamed: R34.1, U4.19 (PB5)
unnamed: C66.2, U4.9 (XTAL1/PB6), Y1.1
unnamed: C65.2, U4.10 (XTAL2/PB7), Y1.2
unnamed: T25.1, U5.8 (ELE0)
unnamed: T26.1, U5.9 (ELE1)
unnamed: T27.1, U5.10 (ELE2)
unnamed: T28.1, U5.11 (ELE3)
unnamed: T29.1, U5.12 (LED0/ELE4)
unnamed: T30.1, U5.13 (LED1/ELE5)
unnamed: T31.1, U5.14 (LED2/ELE6)
unnamed: T32.1, U5.15 (LED3/ELE7)
unnamed: T33.1, U5.16 (LED4/ELE8)
unnamed: T34.1, U5.17 (LED5/ELE9)
unnamed: T35.1, U5.18 (LED6/ELE10)
unnamed: T36.1, U5.19 (LED7/ELE11)
unnamed: R18.2, U5.7 (REXT)
unnamed: C69.1, U5.5 (VREG)
unnamed: T37.1, U6.8 (ELE0)
unnamed: T38.1, U6.9 (ELE1)
unnamed: T39.1, U6.10 (ELE2)
unnamed: T40.1, U6.11 (ELE3)
unnamed: T41.1, U6.12 (LED0/ELE4)
unnamed: T42.1, U6.13 (LED1/ELE5)
unnamed: T43.1, U6.14 (LED2/ELE6)
unnamed: T44.1, U6.15 (LED3/ELE7)
unnamed: T45.1, U6.16 (LED4/ELE8)
unnamed: T46.1, U6.17 (LED5/ELE9)
unnamed: T47.1, U6.18 (LED6/ELE10)
unnamed: T48.1, U6.19 (LED7/ELE11)
unnamed: R22.2, U6.7 (REXT)
unnamed: C72.1, U6.5 (VREG)
unnamed: T49.1, U7.8 (ELE0)
unnamed: T50.1, U7.9 (ELE1)
unnamed: T51.1, U7.10 (ELE2)
unnamed: T52.1, U7.11 (ELE3)
unnamed: T53.1, U7.12 (LED0/ELE4)
unnamed: T54.1, U7.13 (LED1/ELE5)
unnamed: T55.1, U7.14 (LED2/ELE6)
unnamed: T56.1, U7.15 (LED3/ELE7)
unnamed: T57.1, U7.16 (LED4/ELE8)
unnamed: T58.1, U7.17 (LED5/ELE9)
unnamed: T59.1, U7.18 (LED6/ELE10)
unnamed: T60.1, U7.19 (LED7/ELE11)
unnamed: R26.2, U7.7 (REXT)
unnamed: C73.1, U7.5 (VREG)
unnamed: T61.1, U8.8 (ELE0)
unnamed: T62.1, U8.9 (ELE1)
unnamed: T63.1, U8.10 (ELE2)
unnamed: T64.1, U8.11 (ELE3)
unnamed: R30.2, U8.7 (REXT)
unnamed: C74.1, U8.5 (VREG)
VCC: C70.2, C81.2, C82.2, C83.1, J1.2, J3.2 (VCC), R2.1, R31.1, U4.7 (VCC), U4.20 (AVCC), U9.3 (VI); also elsewhere on the board

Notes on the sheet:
Adresse du multiplexeur. Ici on en a qu'un donc par défaut on met tout au GND.
Microcontroleur
Level Shifter
Tout les capteurs peuvent avoir la même interruption, l'avr doit juste checker lequel a fait l'interruption.
Alim
Leds
Régulateur de tension
ISP
Multiplexeur
Touch sensors
